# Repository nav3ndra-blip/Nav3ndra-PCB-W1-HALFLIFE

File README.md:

# Nav3ndra PCB – Week 1 (Hack Club Half Life)

This is my Week 1 PCB project for Hack Club’s Half Life program 2026.
It is a custom hexagon-shaped PCB with my nickname “Nav3ndra*, a 'bass guitar logo', and a 'Spiderman spider logo' added as SVG graphics.

## What’s included
- KiCad project file (`.kicad_pro`)
- PCB layout (`.kicad_pcb`)
- Schematic (`.kicad_sch`)
- Custom SVG graphics used on the board
- My 5-hour progress reel video

## PCB Preview

## About the design
I created this PCB as part of Week 1’s challenge to design a personalized board.  
I chose a hexagon shape and added graphics that represent my interests: bass guitar and Spiderman.

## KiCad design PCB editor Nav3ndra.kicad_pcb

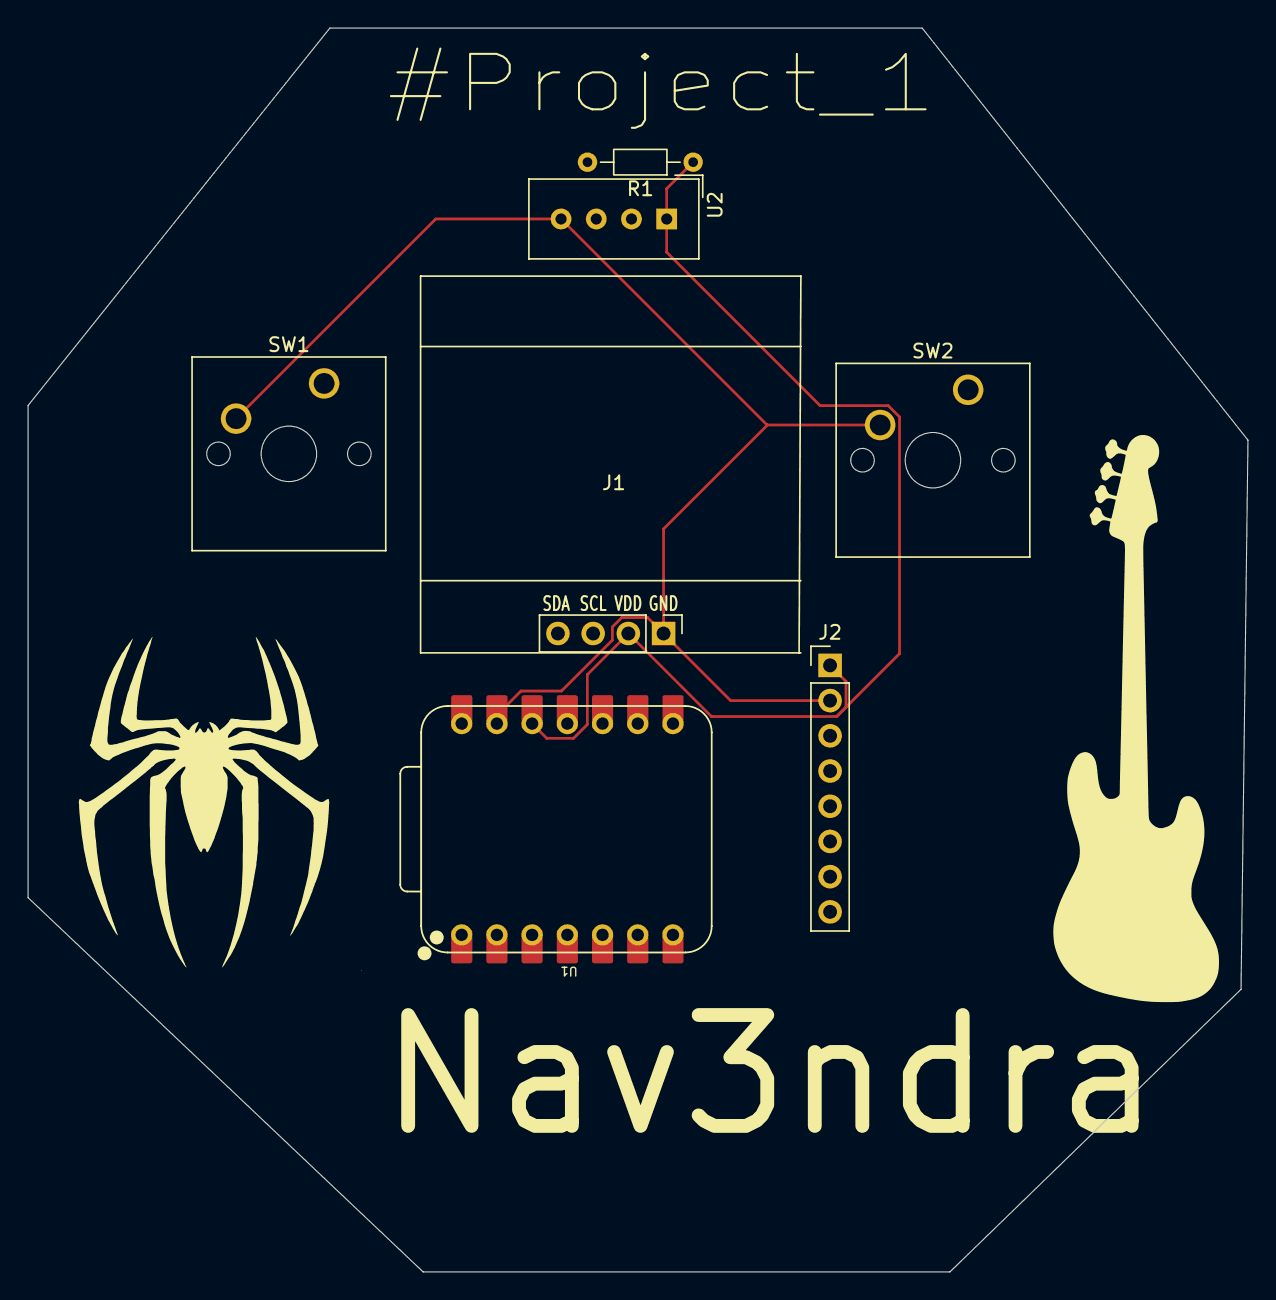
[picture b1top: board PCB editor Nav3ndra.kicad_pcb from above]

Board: 2 copper layers, 88.0 x 89.7 mm, 7 parts (0 on the bottom side), 2 nets.

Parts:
J1: Conn_01x04_Pin; Display_128x64_096_I2C
J2: Conn_01x08_Pin; PinHeader_1x08_P2.54mm_Vertical
R1: R; R_Axial_DIN0204_L3.6mm_D1.6mm_P7.62mm_Horizontal
SW1, SW2: SW_Push; SW_Cherry_MX_1.00u_PCB
U1: XIAO-ESP32-C3-SMD; XIAO-ESP32-C6-DIP
U2: DHT11; Aosong_DHT11_5.5x12.0_P2.54mm

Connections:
+3.3V: J1.2, J2.1, R1.1, U1.12 (3V3_OUT), U2.1 (VDD)
GND: J1.1, J2.2, SW1.2 (2_2), SW2.2 (2_2), U1.13 (GND), U2.4 (GND)
